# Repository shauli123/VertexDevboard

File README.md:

# Vertex Dev-board
A simple RP2040 based dev-board with:
- USB-C Connection
- Flash Memory
- Crystal Oscillator
- Boot Button

Schema:

The Pinout:

The PCB Design:

A 3D Render:

I've always wanted to understand how a devboard works
so i made one myself!
in the way i learnt:
- Why stable power is needed.
- how usb-c even works.
- How SPI & Quad-SPI works.
- What is a flash memory.
- Why do we need a clock(crystal oscillator).
- Why do we need a boot button.
- How to build a schema in kicad.
- How to build a pcb in kicad.
- What is a via.
- What is a copper filled zone.
- What is a diff pair.
- How to pass a DRC.
- How to fabricate.

It was a good journey and if i will have some time maybe i will work on a V2 with a RST Button, Wifi & BLE

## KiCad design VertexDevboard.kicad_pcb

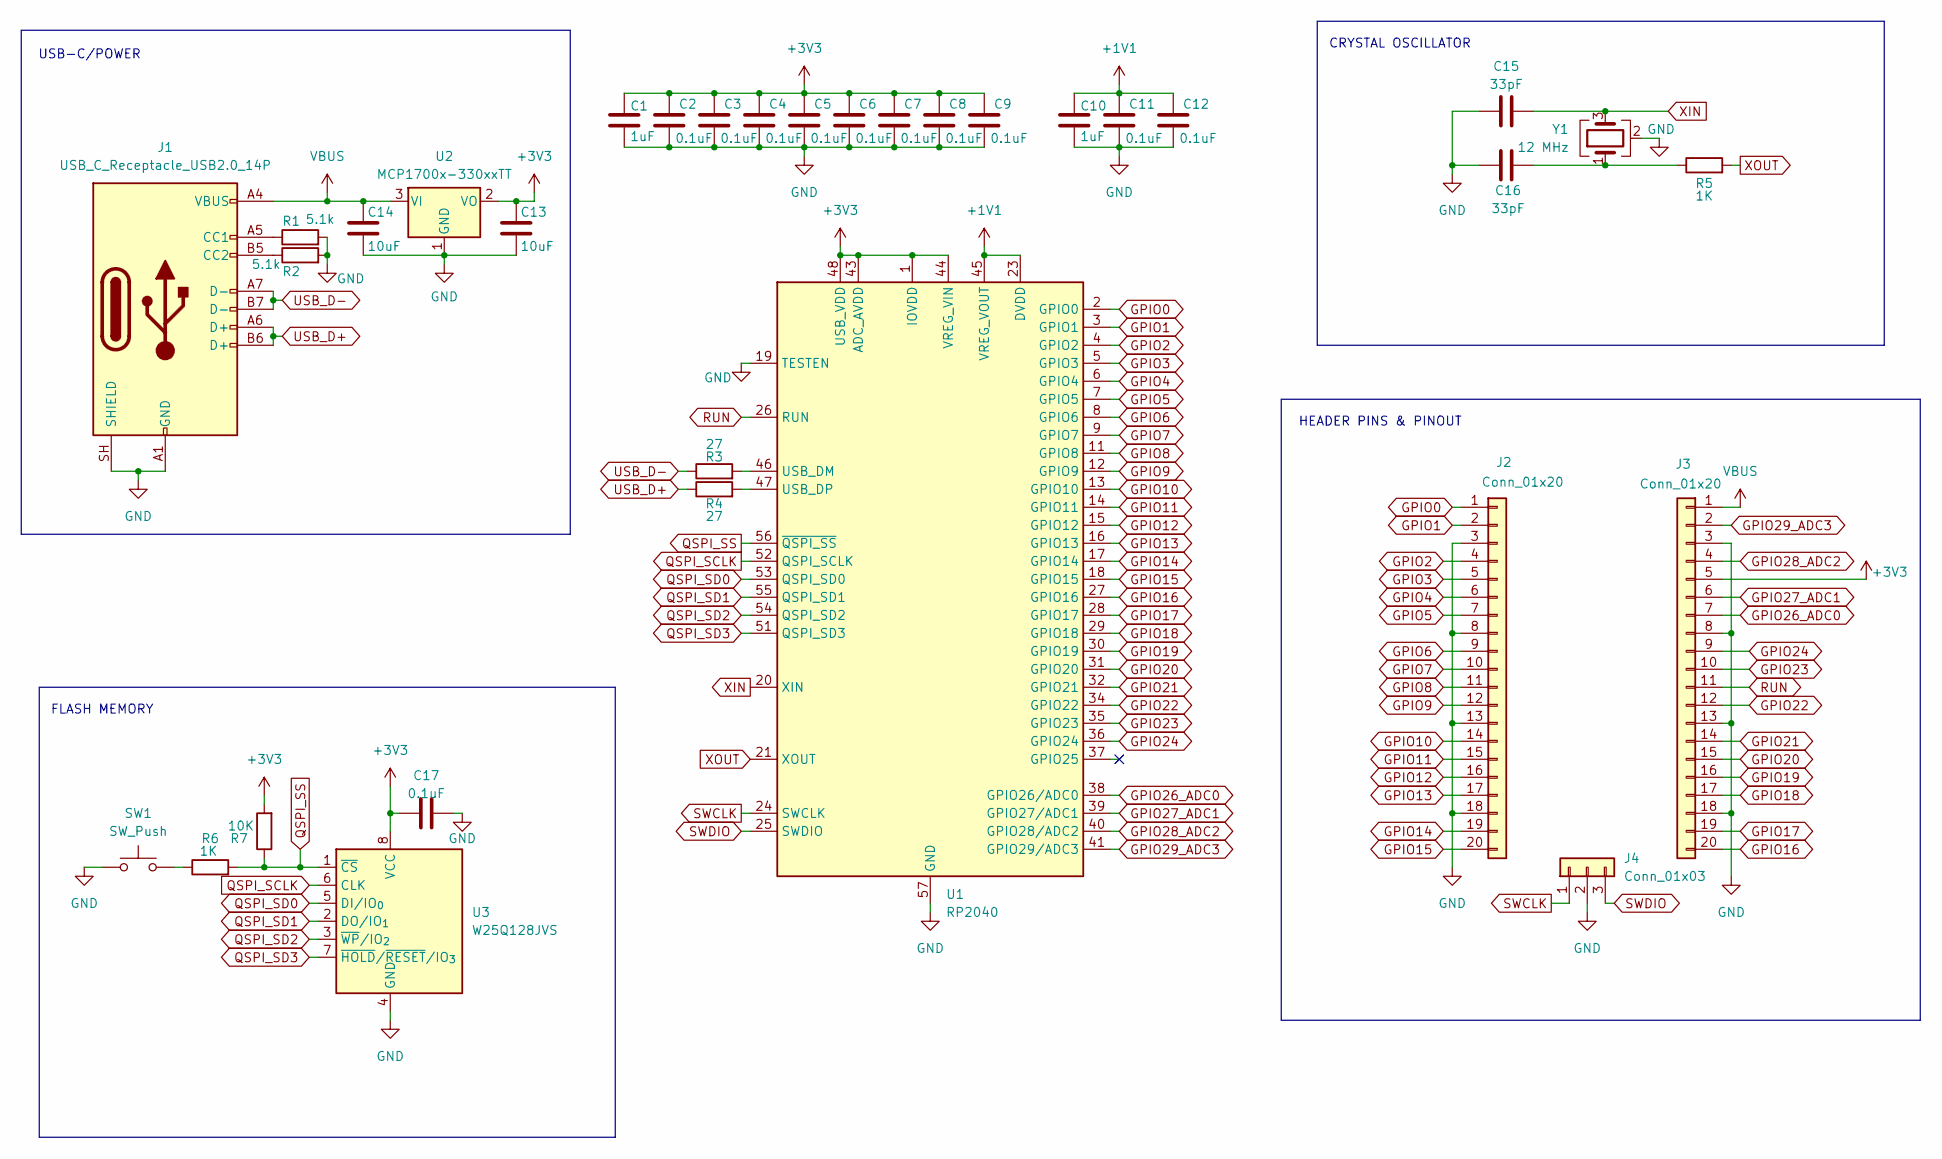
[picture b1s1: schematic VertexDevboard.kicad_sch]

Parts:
C1, C10: 1uF; C_0402_1005Metric
C2, C3, C4, C5, C6, C7, C8, C9, C11, C12, C17: 0.1uF; C_0402_1005Metric
C13, C14: 10uF; C_0603_1608Metric
C15, C16: 33pF; C_0402_1005Metric
J1: USB_C_Receptacle_USB2.0_14P; USB_C_Receptacle_HRO_TYPE-C-31-M-12
J2, J3: Conn_01x20; PinHeader_1x20_P2.54mm_Vertical
J4: Conn_01x03; PinHeader_1x03_P2.54mm_Vertical
R1, R2: 5.1k; R_0402_1005Metric
R3, R4: 27; R_0402_1005Metric
R5, R6: 1K; R_0402_1005Metric
R7: 10K; R_0402_1005Metric
SW1: SW_Push; SW_Push_SPST_NO_Alps_SKRK
U1: RP2040; QFN-56-1EP_7x7mm_P0.4mm_EP3.2x3.2mm
U2: MCP1700x-330xxTT; SOT-23
U3: W25Q128JVS; Winbond_USON-8-1EP_3x2mm_P0.5mm_EP0.2x1.6mm
Y1: 12 MHz; Crystal_SMD_3225-4Pin_3.2x2.5mm

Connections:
+1V1: C10.1, C11.1, C12.1, U1.23 (DVDD), U1.45 (VREG_VOUT), U1.50 (DVDD)
+3V3: C1.1, C2.1, C3.1, C4.1, C5.1, C6.1, C7.1, C8.1, C9.1, C13.1, C17.2, J3.5, R7.2, U1.1 (IOVDD), U1.10 (IOVDD), U1.22 (IOVDD), U1.33 (IOVDD), U1.42 (IOVDD), U1.43 (ADC_AVDD), U1.44 (VREG_VIN), U1.48 (USB_VDD), U1.49 (IOVDD), U2.2 (VO), U3.8 (VCC)
GND: C1.2, C2.2, C3.2, C4.2, C5.2, C6.2, C7.2, C8.2, C9.2, C10.2, C11.2, C12.2, C13.2, C14.2, C15.1, C16.1, C17.1, J1.A1 (GND), J1.A12 (GND), J1.B1 (GND), J1.B12 (GND), J1.SH (SHIELD), J2.3, J2.8, J2.13, J2.18, J3.3, J3.8, J3.13, J3.18, J4.2, R1.2, R2.2, SW1.1, U1.19 (TESTEN), U1.57 (GND), U2.1 (GND), U3.4 (GND), Y1.2 (G), Y1.4 (G)
GPIO0: J2.1, U1.2 (GPIO0)
GPIO1: J2.2, U1.3 (GPIO1)
GPIO2: J2.4, U1.4 (GPIO2)
GPIO3: J2.5, U1.5 (GPIO3)
GPIO4: J2.6, U1.6 (GPIO4)
GPIO5: J2.7, U1.7 (GPIO5)
GPIO6: J2.9, U1.8 (GPIO6)
GPIO7: J2.10, U1.9 (GPIO7)
GPIO8: J2.11, U1.11 (GPIO8)
GPIO9: J2.12, U1.12 (GPIO9)
GPIO10: J2.14, U1.13 (GPIO10)
GPIO11: J2.15, U1.14 (GPIO11)
GPIO12: J2.16, U1.15 (GPIO12)
GPIO13: J2.17, U1.16 (GPIO13)
GPIO14: J2.19, U1.17 (GPIO14)
GPIO15: J2.20, U1.18 (GPIO15)
GPIO16: J3.20, U1.27 (GPIO16)
GPIO17: J3.19, U1.28 (GPIO17)
GPIO18: J3.17, U1.29 (GPIO18)
GPIO19: J3.16, U1.30 (GPIO19)
GPIO20: J3.15, U1.31 (GPIO20)
GPIO21: J3.14, U1.32 (GPIO21)
GPIO22: J3.12, U1.34 (GPIO22)
GPIO23: J3.10, U1.35 (GPIO23)
GPIO24: J3.9, U1.36 (GPIO24)
GPIO26_ADC0: J3.7, U1.38 (GPIO26/ADC0)
GPIO27_ADC1: J3.6, U1.39 (GPIO27/ADC1)
GPIO28_ADC2: J3.4, U1.40 (GPIO28/ADC2)
GPIO29_ADC3: J3.2, U1.41 (GPIO29/ADC3)
unnamed: C16.2, R5.1, Y1.1
unnamed: J1.A5 (CC1), R1.1
unnamed: J1.B5 (CC2), R2.1
unnamed: R6.1, SW1.2
unnamed: R3.2, U1.46 (USB_DM)
unnamed: R4.2, U1.47 (USB_DP)
QSPI_SCLK: U1.52 (QSPI_SCLK), U3.6 (CLK)
QSPI_SD0: U1.53 (QSPI_SD0), U3.5 (DI/IO_{0})
QSPI_SD1: U1.55 (QSPI_SD1), U3.2 (DO/IO_{1})
QSPI_SD2: U1.54 (QSPI_SD2), U3.3 (~WP/IO_{2})
QSPI_SD3: U1.51 (QSPI_SD3), U3.7 (~HOLD/~RESET/IO_{3})
QSPI_SS: R6.2, R7.1, U1.56 (~QSPI_SS), U3.1 (~CS)
RUN: J3.11, U1.26 (RUN)
SWCLK: J4.1, U1.24 (SWCLK)
SWDIO: J4.3, U1.25 (SWDIO)
USB_D+: J1.A6 (D+), J1.B6 (D+), R4.1
USB_D-: J1.A7 (D-), J1.B7 (D-), R3.1
VBUS: C14.1, J1.A4 (VBUS), J1.A9 (VBUS), J1.B4 (VBUS), J1.B9 (VBUS), J3.1, U2.3 (VI)
XIN: C15.2, U1.20 (XIN), Y1.3
XOUT: R5.2, U1.21 (XOUT)

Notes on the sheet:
USB-C/POWER
FLASH MEMORY
CRYSTAL OSCILLATOR
HEADER PINS & PINOUT

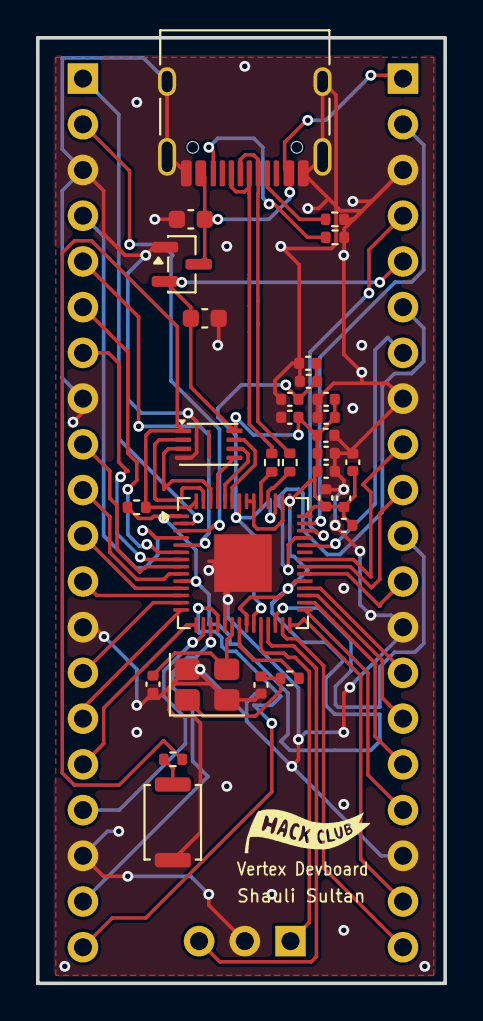
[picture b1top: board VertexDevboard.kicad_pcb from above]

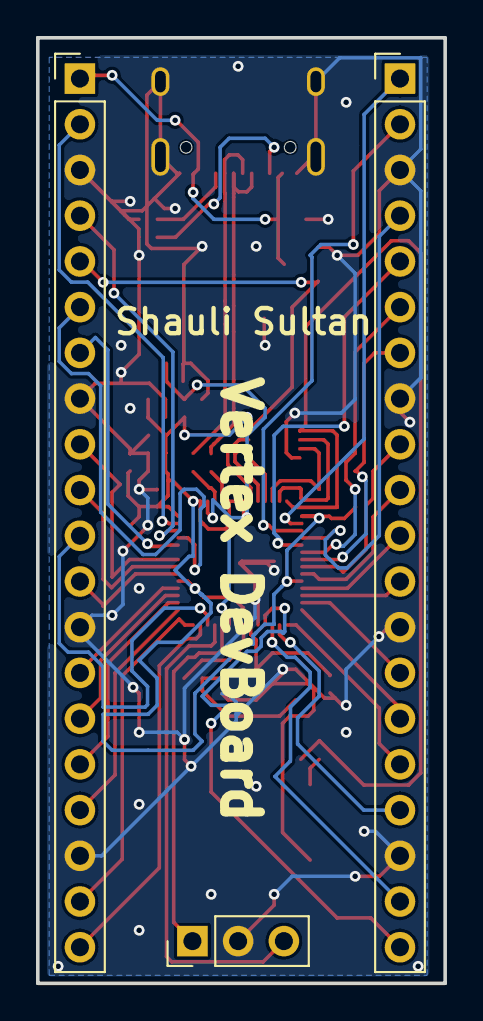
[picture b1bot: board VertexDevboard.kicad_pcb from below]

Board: 2 copper layers, 22.6 x 52.5 mm, 33 parts (3 on the bottom side), 52 nets.

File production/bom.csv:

Designator,Footprint,Quantity,Value,LCSC Part #
"C1, C10",0402,2,1uF,
"C11, C12, C17, C2, C3, C4, C5, C6, C7, C8, C9",0402,11,0.1uF,
"C13, C14",0603,2,10uF,
"C15, C16",0402,2,33pF,
J1,USB_C_Receptacle_HRO_TYPE-C-31-M-12,1,USB_C_Receptacle_USB2.0_14P,
"J2, J3",PinHeader_1x20_P2.54mm_Vertical,2,Conn_01x20,
J4,PinHeader_1x03_P2.54mm_Vertical,1,Conn_01x03,
"R1, R2",0402,2,5.1k,
"R3, R4",0402,2,27,
"R5, R6",0402,2,1K,
R7,0402,1,10K,
SW1,SW_Push_SPST_NO_Alps_SKRK,1,SW_Push,
U1,QFN-56-1EP_7x7mm_P0.4mm_EP3.2x3.2mm,1,RP2040,
U2,SOT-23,1,MCP1700x-330xxTT,
U3,Winbond_USON-8-1EP_3x2mm_P0.5mm_EP0.2x1.6mm,1,W25Q128JVS,
Y1,Crystal_SMD_3225-4Pin_3.2x2.5mm,1,12 MHz,

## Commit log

2026-05-17 pbc 1
2026-05-17 DRC OK
2026-05-17 Before fabric
2026-05-17 Before fabric 0 DRC Erros
2026-05-18 first prod
2026-05-21 prod ready
2026-05-21 final v1
